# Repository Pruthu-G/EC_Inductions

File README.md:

# Inductions

Hello and welcome to the official github repository for Project Kratos Inductions 2025! This repository is where you will be making your assignment submissions, and also learning how to use git.

### What is git?

Git is a software used to do "version control" and track changes in code. Github is where this code is hosted. [Watch this video](https://youtu.be/r8jQ9hVA2qs?si=RhdH97FD-Xc3-4q8) to learn more 

### Installation 

Follow this [link](https://git-scm.com/book/en/v2/Getting-Started-Installing-Git) for instructions on how to install git on your system. (_do contact us if you face any issues_)

### Set Up

You will now need to setup your git, by configuring your username and email id, [check this out](https://docs.github.com/en/get-started/git-basics/set-up-git)

### Submission 

Clone this repository onto your systems using the following command 
```bash
git clone https://github.com/Pruthu-G/EC_Inductions.git
```
And you will find a folder named _EC_Inductions_ in the directory where you ran it. 

now change your directory to this folder using the ```cd``` command

Now, create a branch with the name of the folling format : **<first_name>_<last_name>** 
```bash
git branch <first_name>_<last_name>
```
Then, switch to your designated branch (_do not mess with anyone elses branch **we will find out**_)

```bash
git checkout <first_name>_<last_name>
```

Now youre all set up! To add your files and commit them to your branch for the first time
```bash
git add .
git commit -m "enter meaningful message here"
git push -u origin <first_name>_<last_name>
```
After you have let git know your branch of choice using the ``` -u ``` tag, you can simply type ```git push``` for all further additions. 

---
>💡 Tip : **It is always good to make sure that you are in the current branch, use ```git branch``` to verify, always**
---

mic check

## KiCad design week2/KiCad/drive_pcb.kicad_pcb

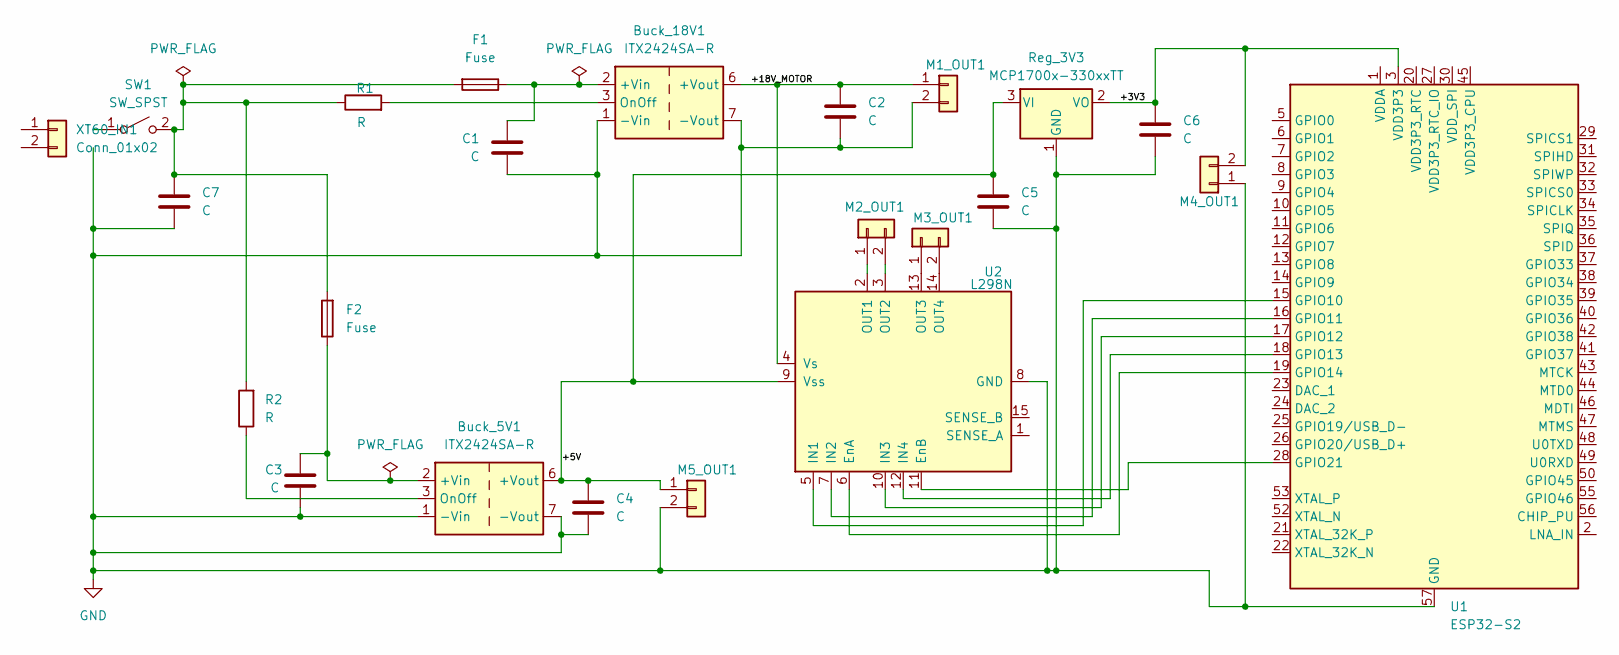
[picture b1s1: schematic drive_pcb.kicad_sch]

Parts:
Buck_5V1, Buck_18V1: ITX2424SA-R; Converter_DCDC_XP_POWER-ITxxxxxS_THT
C1, C2, C3, C4, C5, C6, C7: C; CP_Radial_D5.0mm_P2.50mm
F1, F2: Fuse; Fuseholder_Keystone_3555-2
M1_OUT1, M2_OUT1, M4_OUT1, M5_OUT1: Conn_01x02; PinHeader_1x02_P2.54mm_Horizontal
M3_OUT1: PinHeader_1x02_P2.54mm_Horizontal
R1, R2: R; R_Axial_DIN0207_L6.3mm_D2.5mm_P10.16mm_Horizontal
Reg_3V3: MCP1700x-330xxTT; SOT-23
SW1: SW_SPST; SW_SPST_Omron_B3F-40xx
U1: ESP32-S2; QFN-56-1EP_7x7mm_P0.4mm_EP4x4mm
U2: L298N; DIP-16_W7.62mm
XT60_IN1: Conn_01x02; AMASS_XT30U-M_1x02_P5.0mm_Vertical

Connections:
/+3V3: C6.1, M4_OUT1.2, Reg_3V3.2 (VO), U1.3 (VDD3P3), U1.4 (VDD3P3)
/+5V: Buck_5V1.6 (+Vout), C4.1, C5.1, M5_OUT1.1, Reg_3V3.3 (VI), U2.9 (Vss)
/+18V_MOTOR: Buck_18V1.6 (+Vout), C2.1, M1_OUT1.1, U2.4 (Vs)
GND: Buck_5V1.1 (-Vin), Buck_5V1.7 (-Vout), Buck_18V1.1 (-Vin), Buck_18V1.7 (-Vout), C1.2, C2.2, C3.2, C4.2, C5.2, C6.2, C7.2, M1_OUT1.2, M4_OUT1.1, M5_OUT1.2, Reg_3V3.1 (GND), U1.57 (GND), U2.8 (GND)
unnamed: Buck_5V1.2 (+Vin), C3.1, F2.1
unnamed: Buck_5V1.3 (OnOff), R2.1
unnamed: Buck_18V1.2 (+Vin), C1.1, F1.1
unnamed: Buck_18V1.3 (OnOff), R1.2
unnamed: M2_OUT1.1, U2.2 (OUT1)
unnamed: M2_OUT1.2, U2.3 (OUT2)
unnamed: M3_OUT1.1, U2.13 (OUT3)
unnamed: M3_OUT1.2, U2.14 (OUT4)
unnamed: C7.1, F1.2, F2.2, R1.1, R2.2, SW1.2 (B)
unnamed: U1.15 (GPIO10), U2.5 (IN1)
unnamed: U1.16 (GPIO11), U2.7 (IN2)
unnamed: U1.17 (GPIO12), U2.10 (IN3)
unnamed: U1.18 (GPIO13), U2.12 (IN4)
unnamed: U1.19 (GPIO14), U2.6 (EnA)
unnamed: U1.28 (GPIO21), U2.11 (EnB)
unnamed: U1.1 (VDDA), U1.51 (VDDA), U1.54 (VDDA)

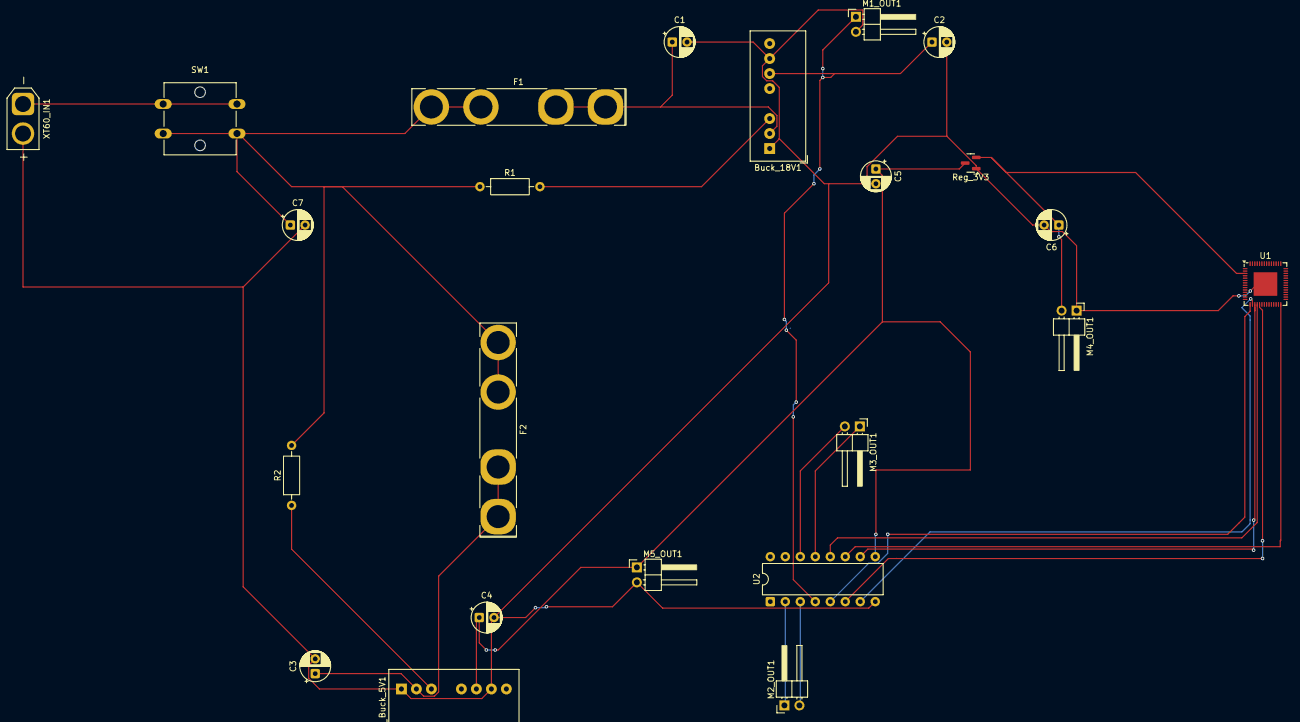
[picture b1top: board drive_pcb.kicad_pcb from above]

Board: 2 copper layers, 23 parts (0 on the bottom side), 20 nets.

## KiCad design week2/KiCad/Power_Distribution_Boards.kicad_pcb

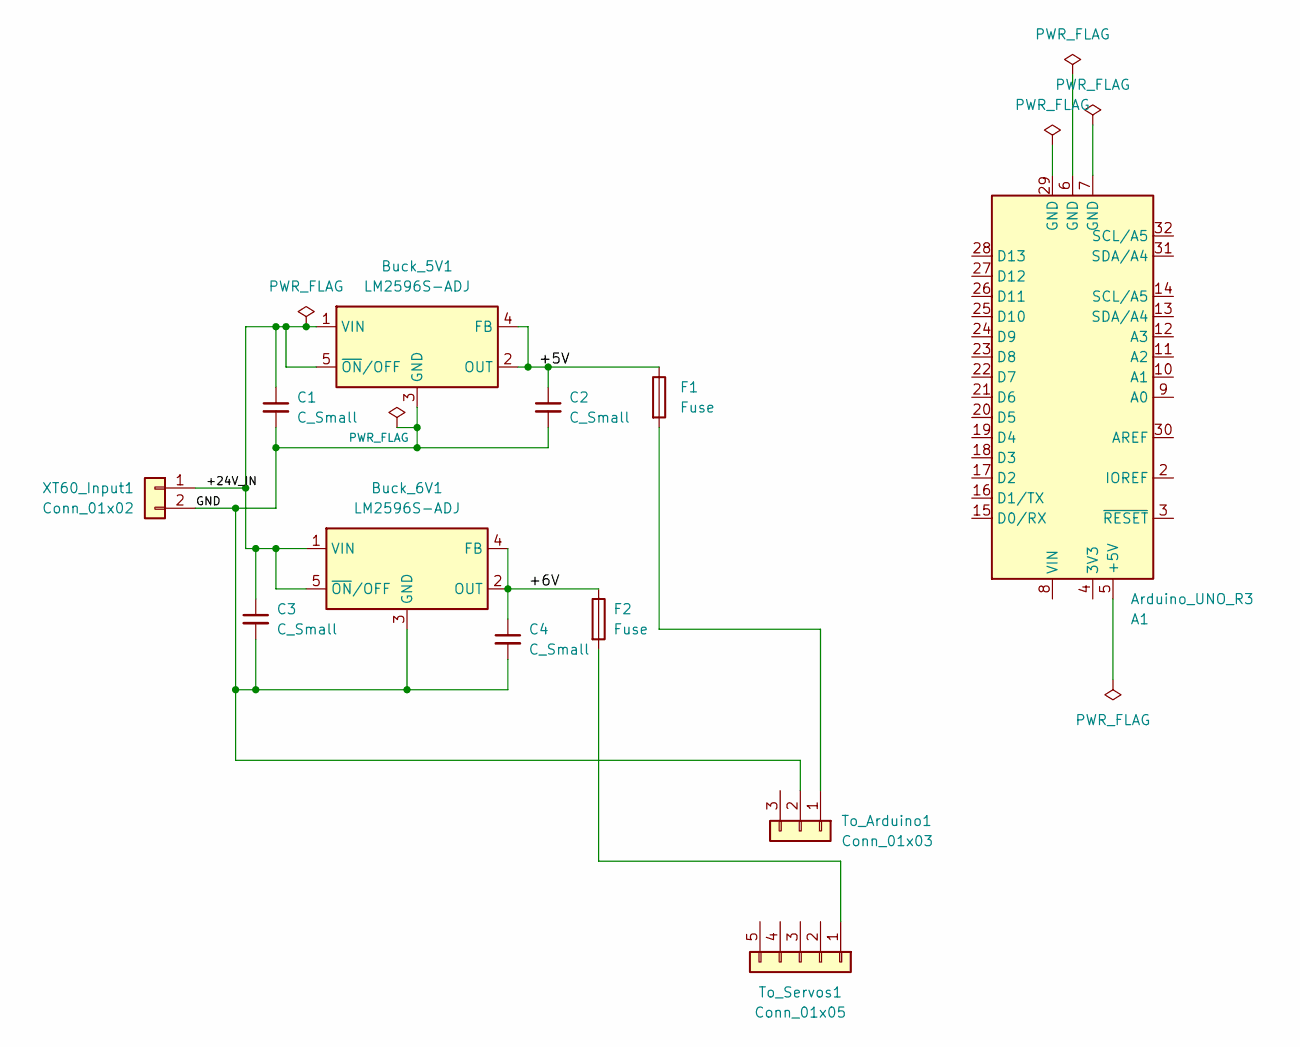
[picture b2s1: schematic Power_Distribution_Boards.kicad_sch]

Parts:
A1: Arduino_UNO_R3
Buck_5V1, Buck_6V1: LM2596S-ADJ; TO-263-5_TabPin3
C1, C2, C3, C4: C_Small; C_Disc_D5.0mm_W2.5mm_P2.50mm
F1, F2: Fuse
To_Arduino1: Conn_01x03
To_Servos1: Conn_01x05
XT60_Input1: Conn_01x02

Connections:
/+5V: Buck_5V1.2 (OUT), Buck_5V1.4 (FB), C2.1, F1.1
/+6V: Buck_6V1.2 (OUT), Buck_6V1.4 (FB), C4.1, F2.1
/+24V_IN: Buck_5V1.1 (VIN), Buck_5V1.5 (~ON/OFF), Buck_6V1.1 (VIN), Buck_6V1.5 (~ON/OFF), C1.1, C3.1, XT60_Input1.1
/GND: Buck_5V1.3 (GND), Buck_6V1.3 (GND), C1.2, C2.2, C3.2, C4.2, To_Arduino1.2, XT60_Input1.2
unnamed: F1.2, To_Arduino1.1
unnamed: F2.2, To_Servos1.1

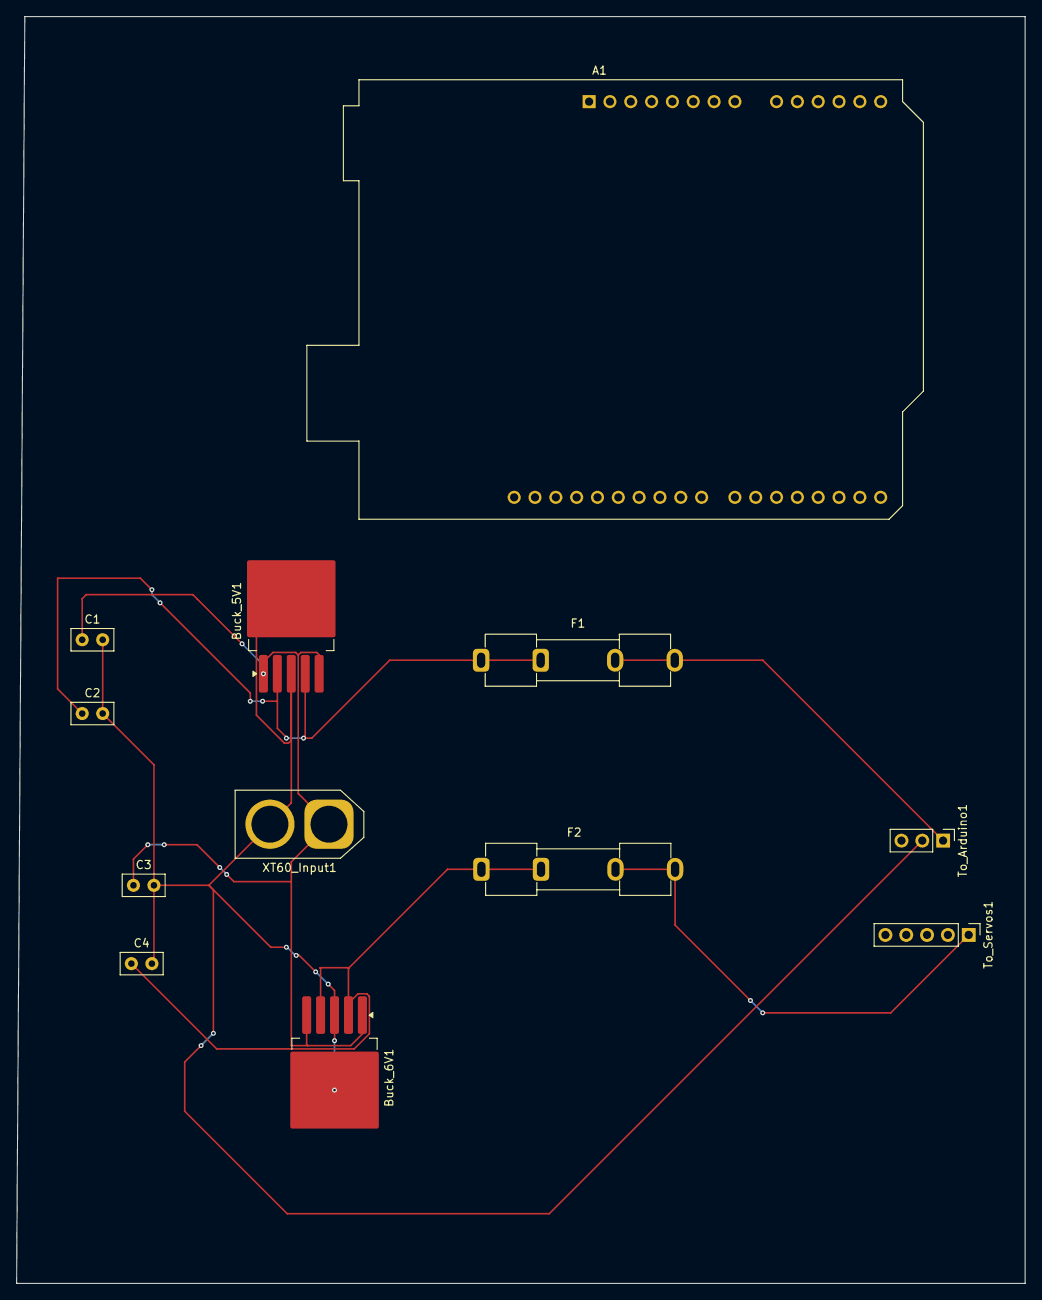
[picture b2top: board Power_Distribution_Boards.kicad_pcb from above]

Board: 2 copper layers, 123.0 x 154.5 mm, 12 parts (0 on the bottom side), 6 nets.

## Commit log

2025-06-12 hello world
2025-06-17 Create rover_object_model.py
    first commit
2025-06-17 week1 rover
2025-06-17 mic check
2025-06-17 python assignment
2025-06-18 this took way too much time
2025-06-18 Rename week1.py to rover_object.py
2025-06-18 Updated rover_object.py for jagged map
2025-06-18 Update rover_object.py, removed unnecessary import
2025-06-18 Add Rover Object Model assignment
2025-06-19 Adding week1 assignment
2025-06-21 Question 2 submission
2025-06-22 week 1 python assignment submission :)
2025-06-22 First commit
    Created Position with attributes
2025-06-22 improved comment
2025-06-22 added week1 submission #1
2025-06-22 added rover.py for week1 submission
2025-06-22 cleaned empty lines, cleaned main function
2025-06-22 Week 1 - Question 2
2025-06-22 Deleted random file that got pushed
2025-06-22 Adding python file.
2025-06-22 week1
2025-06-23 added assignment files
2025-06-23 Revert "Adding python file."
2025-06-23 behind schedule but updated, regardless
2025-06-23 enter meaningful message here
2025-06-23 Add week1 folder and move Python script inside
2025-07-12 Create new file
2025-08-06 Created using Colab
2025-08-06 week_2
